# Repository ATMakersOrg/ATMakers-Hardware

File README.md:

# ATMakers-Hardware
PCB Design files and other hardware artifacts from ATMakers.org

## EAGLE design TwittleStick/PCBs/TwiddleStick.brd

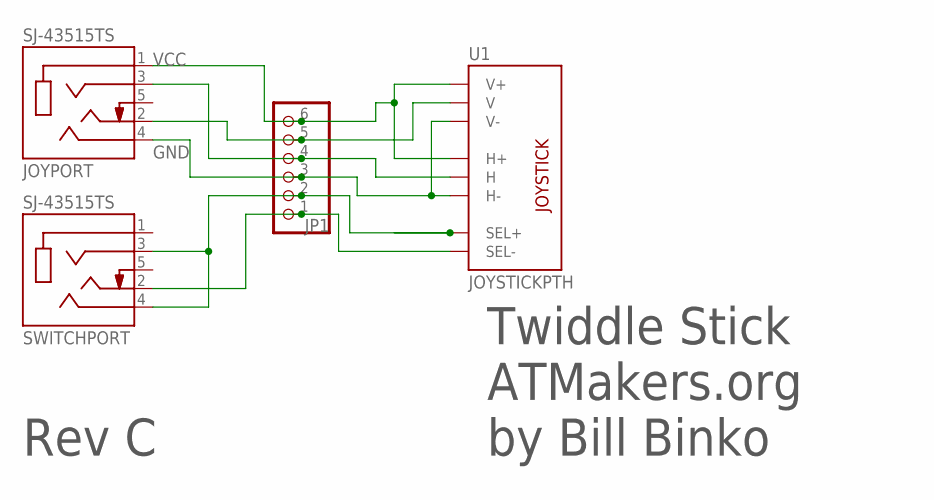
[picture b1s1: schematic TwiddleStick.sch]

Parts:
JOYPORT: SJ-43515TS; CUI_SJ-43515TS
JP1: PINHD-1X6B; 1X06-BIG
SWITCHPORT: SJ-43515TS; CUI_SJ-43515TS
U1: JOYSTICKPTH; JOYSTICK

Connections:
GND: JOYPORT.4 (RING2), JP1.3, U1.H3 (H-), U1.V3 (V-)
unnamed: JP1.2, SWITCHPORT.3 (RING1), SWITCHPORT.4 (RING2), U1.B1A (SEL+)
unnamed: JOYPORT.2 (TIP), JP1.5, U1.V2 (V)
unnamed: JOYPORT.3 (RING1), JP1.4, U1.H2 (H)
unnamed: JP1.1, SWITCHPORT.2 (TIP), U1.B2A (SEL-)
VCC: JOYPORT.1 (SLEEVE), JP1.6, U1.H1 (H+), U1.V1 (V+)

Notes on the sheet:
Twiddle Stick ATMakers.org by Bill Binko
Rev C

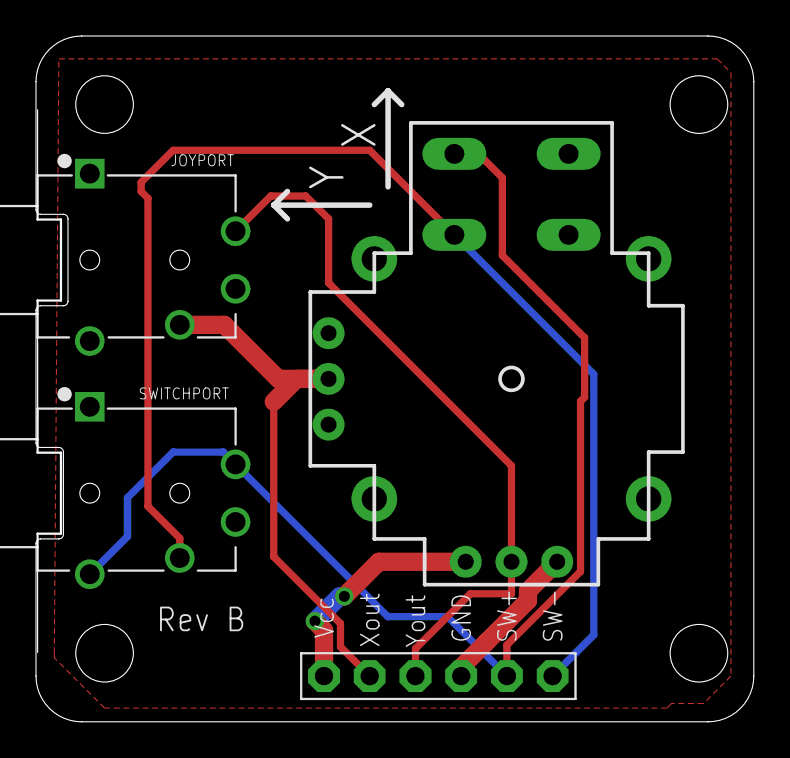
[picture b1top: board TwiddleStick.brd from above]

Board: 2 copper layers, 39.9 x 38.1 mm, 4 parts (0 on the bottom side), 6 nets.

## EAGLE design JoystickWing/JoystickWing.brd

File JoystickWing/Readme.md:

This is a PTH-only design that should be simple to assemble.  It has a FeatherWing format and should allow a microcontroller to interface with a PG-Drives powerchair controller.

The design was based off of the details in section 6 of this manual: http://sunrise.pgdrivestechnology.com/manuals/pgdt_omni_manual_SK78813-07.pdf

It is based on the Adafruit DS3502 Digital Pot breakout
https://learn.adafruit.com/ds3502-i2c-potentiometer/overview

It uses this D-Sub 9 panel-mount connector
https://www.digikey.com/products/en?keywords=5747844-4

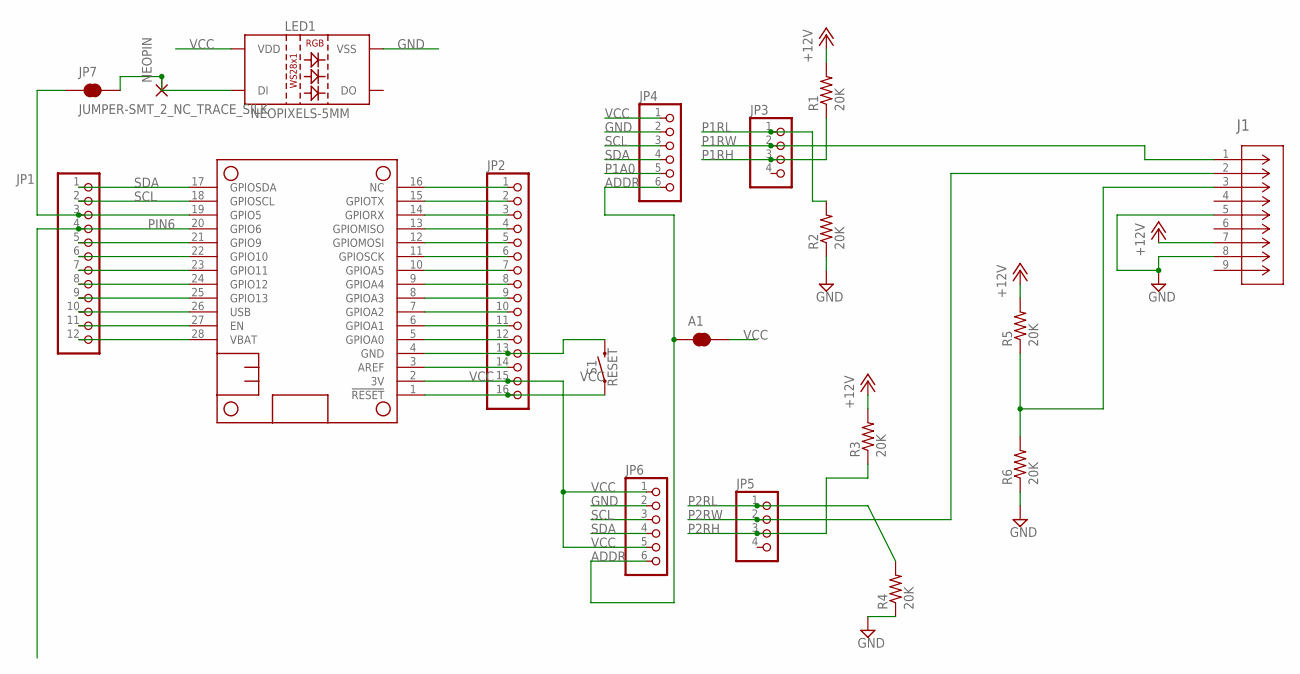
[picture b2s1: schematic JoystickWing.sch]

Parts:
A1: JUMPER-SMT_2_NC_TRACE_SILK; SMT-JUMPER_2_NC_TRACE_SILK
J1: 5747844-4; CONN_5747844-4
JP1: PINHD-1X12; 1X12
JP2: PINHD-1X16; 1X16
JP3, JP5: HEADER-1X4ROUND; 1X04_ROUND
JP4, JP6: HEADER-1X6ROUND; 1X06_ROUND
JP7: JUMPER-SMT_2_NC_TRACE_SILK; SMT-JUMPER_2_NC_TRACE_SILK
LED1: NEOPIXELS-5MM
MS1: FEATHERWING_NODIM; FEATHERWING_DIM
NEOPIN: 2,54/1,1
R1, R2, R3, R4, R5, R6: 20K; 0204/7
S1: RESET; DTS-3

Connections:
+12V: J1.7, R1.2, R3.2, R5.2
ADDR: A1.1, JP4.6, JP6.6
GND: J1.5, J1.8, JP2.13, JP4.2, JP6.2, LED1.P3 (VSS), MS1.4 (GND), R2.1, R4.1, R6.1, S1.2
unnamed: JP1.3, JP7.1, MS1.19 (GPIO5)
unnamed: JP1.5, MS1.21 (GPIO9)
unnamed: JP1.6, MS1.22 (GPIO10)
unnamed: JP1.7, MS1.23 (GPIO11)
unnamed: JP1.8, MS1.24 (GPIO12)
unnamed: J1.3, R5.1, R6.2
unnamed: JP1.9, MS1.25 (GPIO13)
unnamed: JP1.11, MS1.27 (EN)
unnamed: JP2.1, MS1.16 (NC)
unnamed: JP2.2, MS1.15 (GPIOTX)
unnamed: JP2.3, MS1.14 (GPIORX)
unnamed: JP2.4, MS1.13 (GPIOMISO)
unnamed: JP2.5, MS1.12 (GPIOMOSI)
unnamed: JP2.6, MS1.11 (GPIOSCK)
unnamed: JP2.7, MS1.10 (GPIOA5)
unnamed: JP2.8, MS1.9 (GPIOA4)
unnamed: JP2.9, MS1.8 (GPIOA3)
unnamed: JP2.10, MS1.7 (GPIOA2)
unnamed: JP2.11, MS1.6 (GPIOA1)
unnamed: JP2.12, MS1.5 (GPIOA0)
unnamed: JP2.14, MS1.3 (AREF)
unnamed: JP2.16, MS1.1 (!RESET), S1.1
unnamed: JP7.2, LED1.P1 (DI), NEOPIN.1
P1A0: JP4.5
P1RH: JP3.3, R1.1
P1RL: JP3.1, R2.2
P1RW: J1.1, JP3.2
P2RH: JP5.3, R3.1
P2RL: JP5.1, R4.2
P2RW: J1.2, JP5.2
PIN6: JP1.4, MS1.20 (GPIO6)
SCL: JP1.2, JP4.3, JP6.3, MS1.18 (GPIOSCL)
SDA: JP1.1, JP4.4, JP6.4, MS1.17 (GPIOSDA)
USB: JP1.10, MS1.26 (USB)
VBAT: JP1.12, MS1.28 (VBAT)
VCC: A1.2, JP2.15, JP4.1, JP6.1, JP6.5, LED1.P2 (VDD), MS1.2 (3V)

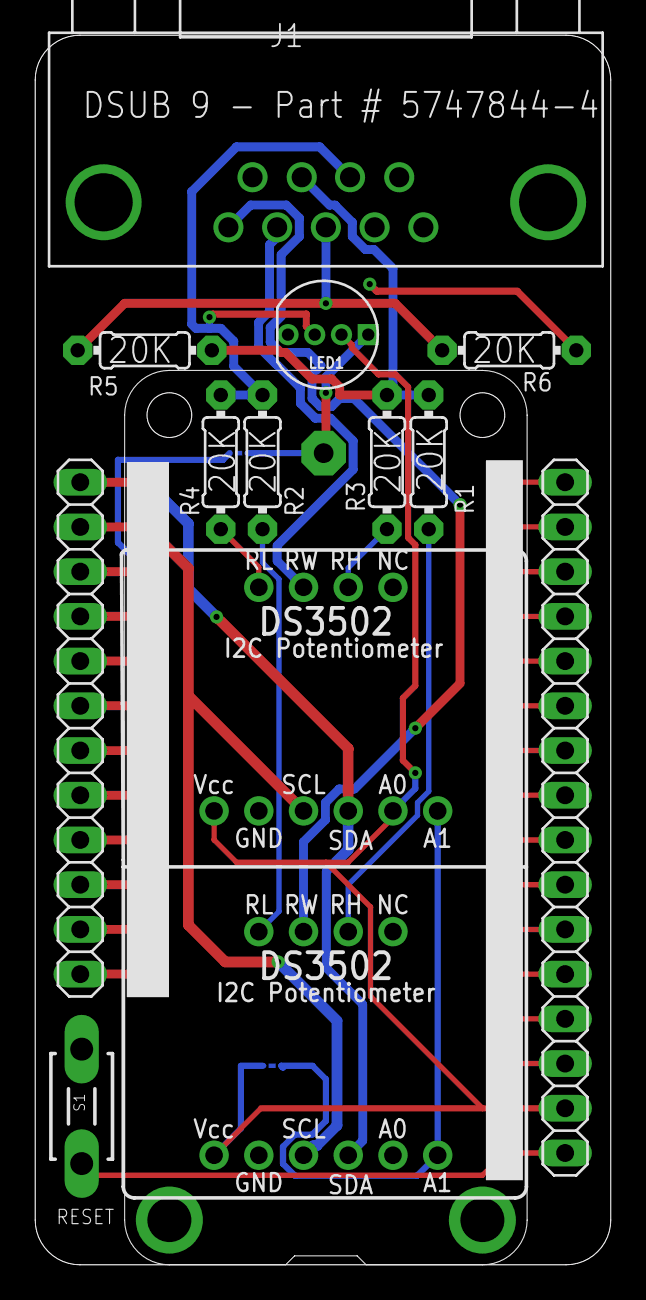
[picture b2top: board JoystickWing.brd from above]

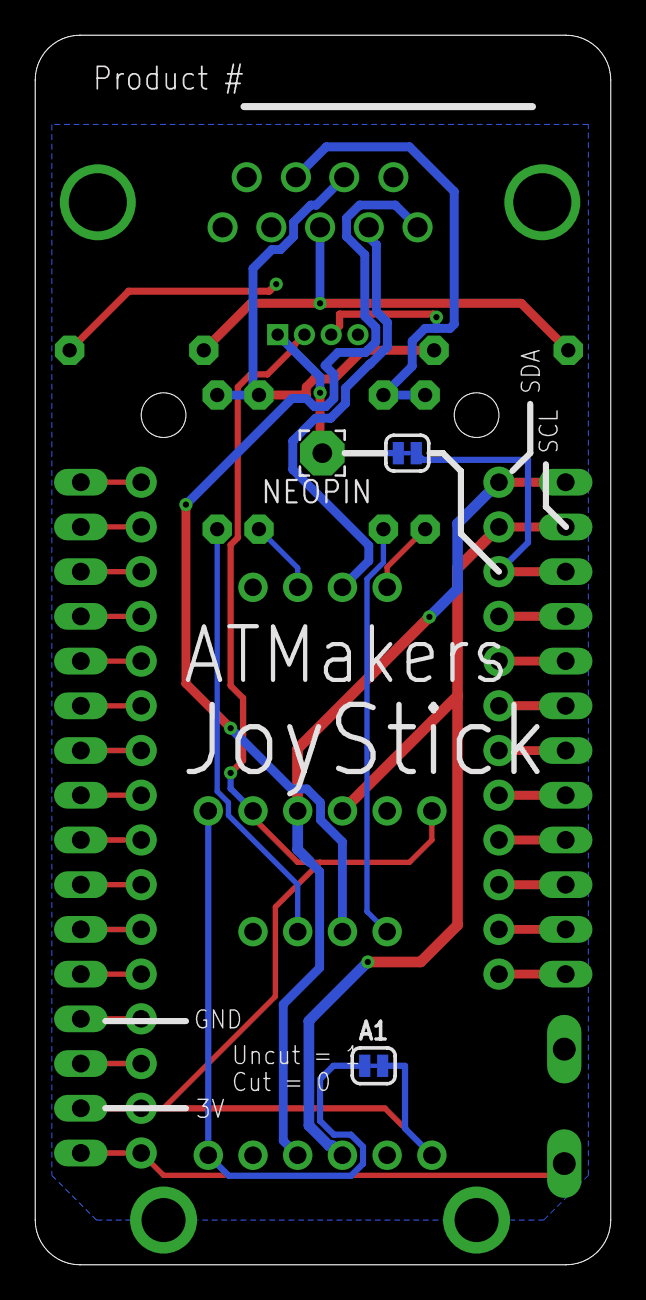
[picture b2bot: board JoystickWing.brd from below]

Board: 2 copper layers, 32.7 x 69.8 mm, 19 parts (3 on the bottom side), 38 nets.

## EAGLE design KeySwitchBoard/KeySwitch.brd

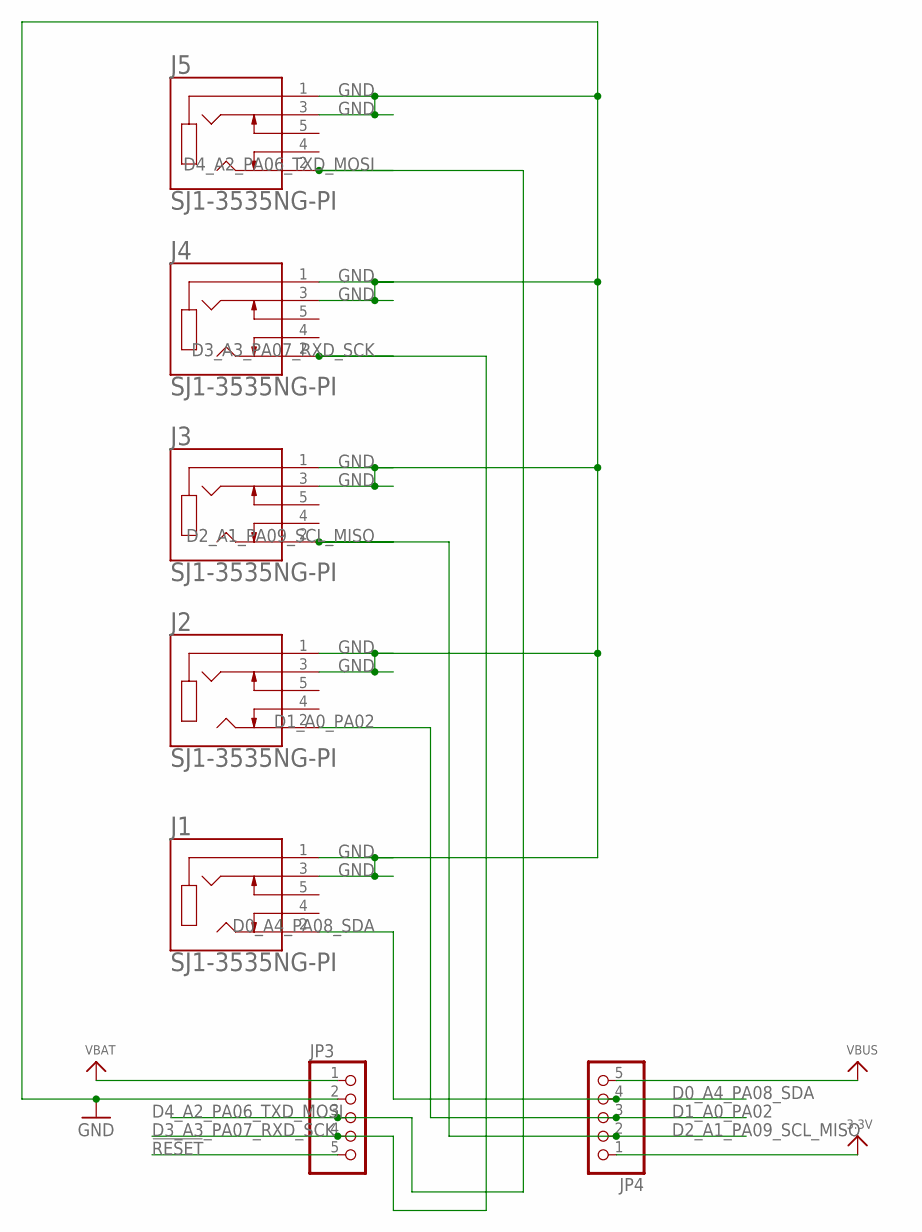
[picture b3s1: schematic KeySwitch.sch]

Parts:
J1, J2, J3, J4, J5: SJ1-3535NG-PI; CUI_SJ1-3535NG-PI
JP3, JP4: HEADER-1X576MIL; 1X05_ROUND_76

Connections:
3.3V: JP4.1
!RESET: JP3.5
D0_A4_PA08_SDA: J1.2, JP4.4
D1_A0_PA02: J2.2, JP4.3
D2_A1_PA09_SCL_MISO: J3.2, JP4.2
D3_A3_PA07_RXD_SCK: J4.2, JP3.4
D4_A2_PA06_TXD_MOSI: J5.2, JP3.3
GND: J1.1, J1.3, J2.1, J2.3, J3.1, J3.3, J4.1, J4.3, J5.1, J5.3, JP3.2
VBAT: JP3.1
VBUS: JP4.5

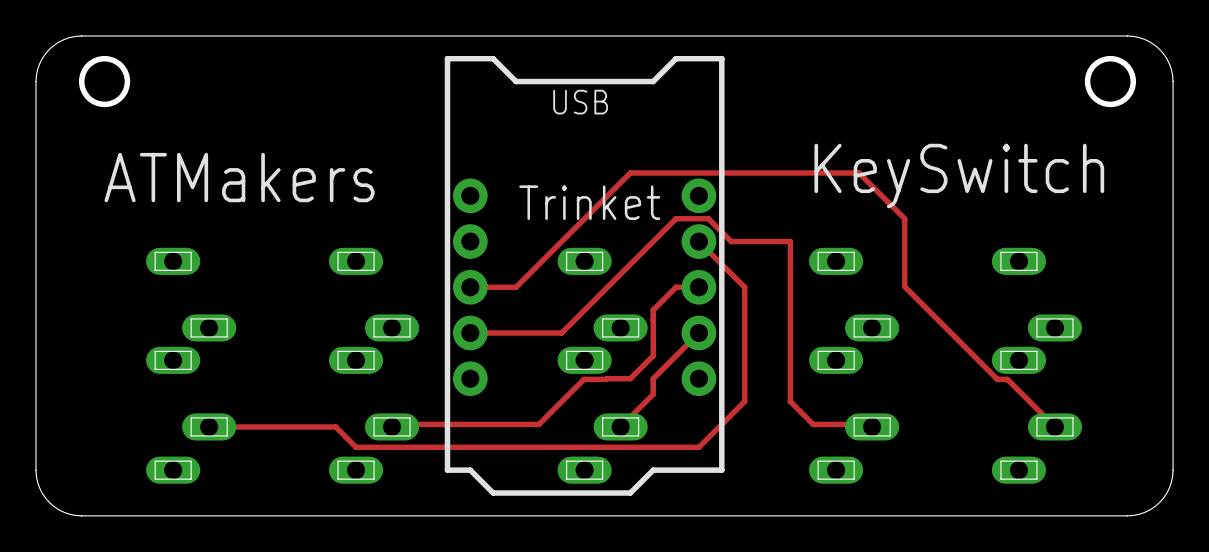
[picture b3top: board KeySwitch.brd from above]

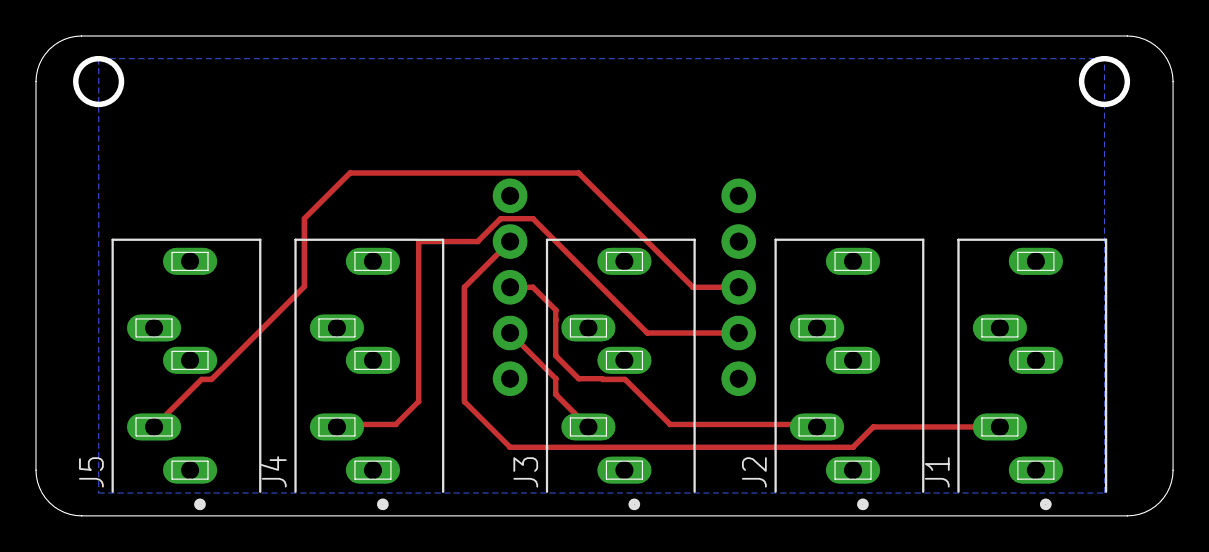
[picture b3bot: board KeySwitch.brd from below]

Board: 2 copper layers, 63.2 x 26.7 mm, 7 parts (5 on the bottom side), 6 nets.

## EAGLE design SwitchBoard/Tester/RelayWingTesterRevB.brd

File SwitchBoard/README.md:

# ATMakers-Hardware-SwitchBoard
Eagle CAD PCB Design files and other product information for the 5-Relay Switchboard Feather Wing.

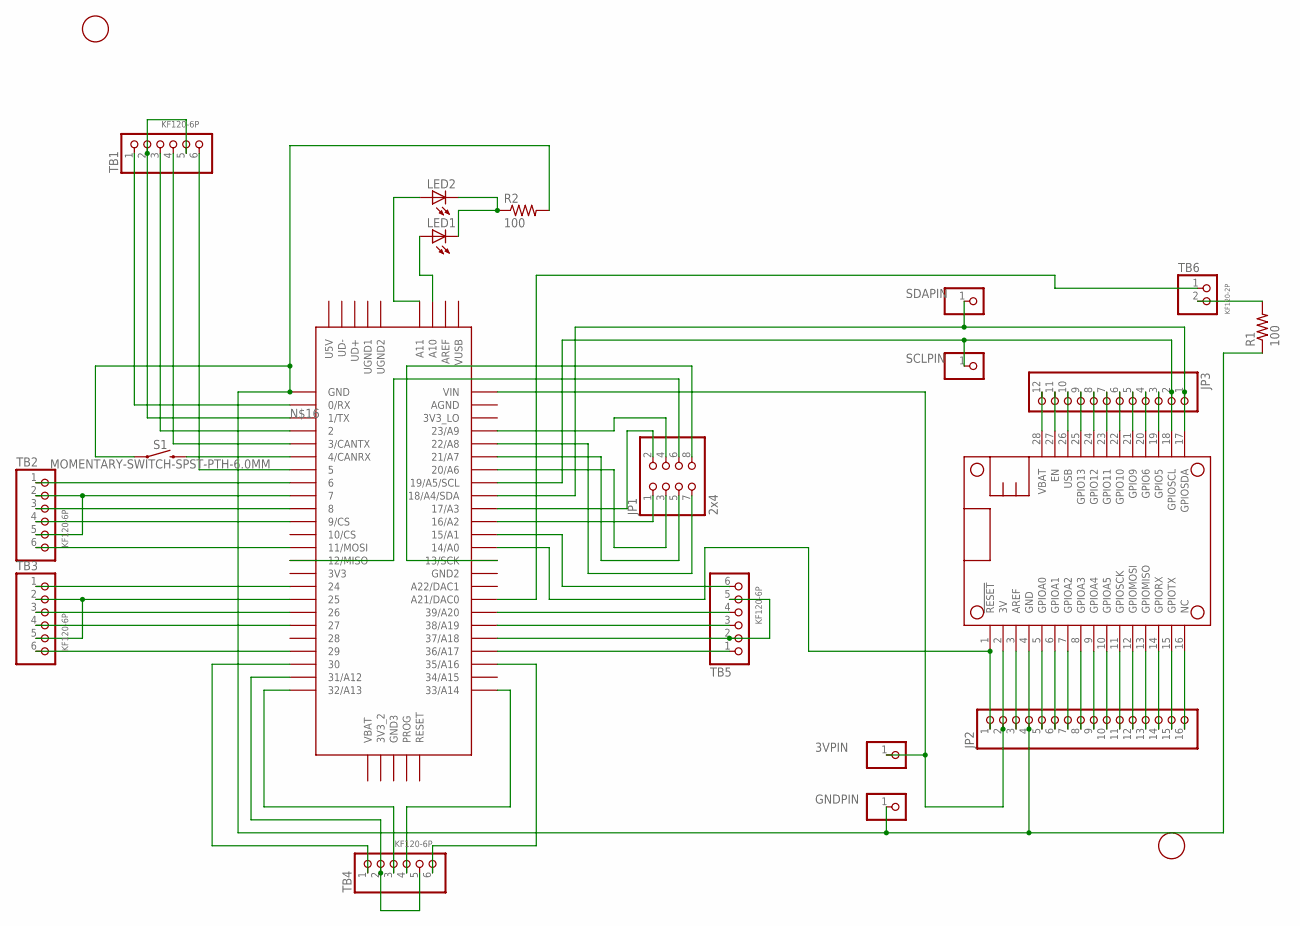
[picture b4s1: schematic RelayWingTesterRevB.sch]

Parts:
3VPIN: PINHD-1X1; 1X01
GNDPIN: PINHD-1X1; 1X01
JP1: 2x4; 2X04
JP2: PINHD-1X16; 1X16
JP3: PINHD-1X12; 1X12
LED1, LED2: LED5MM
MS1: FEATHERWING_NODIM; FEATHERWING_DIM
R1, R2: 100; 0207/10
S1: MOMENTARY-SWITCH-SPST-PTH-6.0MM; TACTILE_SWITCH_PTH_6.0MM
SCLPIN: PINHD-1X1; 1X01
SDAPIN: PINHD-1X1; 1X01
TB1, TB2, TB3, TB4, TB5: KF120-6P; KF120-6P_ROUND
TB6: KF120-2P; KF120-2P_ROUND
U$2, U$3: FIDUCIAL; FIDUCIAL_1MM
U$4: TEENSY_3.5/3.6

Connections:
3V: 3VPIN.1, JP2.2, MS1.2 (3V), U$4.VIN
GND: GNDPIN.1, JP2.4, MS1.4 (GND), R1.1, R2.2, S1.1, U$4.GND
unnamed: JP2.3, MS1.3 (AREF)
unnamed: JP3.1, MS1.17 (GPIOSDA), SDAPIN.1, U$4.18/A4/SDA
unnamed: JP2.5, MS1.5 (GPIOA0)
unnamed: JP2.6, MS1.6 (GPIOA1)
unnamed: JP2.7, MS1.7 (GPIOA2)
unnamed: JP2.8, MS1.8 (GPIOA3)
unnamed: JP2.9, MS1.9 (GPIOA4)
unnamed: JP2.10, MS1.10 (GPIOA5)
unnamed: JP2.11, MS1.11 (GPIOSCK)
unnamed: JP2.12, MS1.12 (GPIOMOSI)
unnamed: JP2.13, MS1.13 (GPIOMISO)
unnamed: JP2.14, MS1.14 (GPIORX)
unnamed: JP2.15, MS1.15 (GPIOTX)
unnamed: JP2.16, MS1.16 (NC)
unnamed: JP3.3, MS1.19 (GPIO5)
unnamed: TB1.1, U$4.0/RX
unnamed: TB1.2, TB1.5, U$4.1/TX
unnamed: R1.2, TB6.2
unnamed: JP3.4, MS1.20 (GPIO6)
unnamed: JP3.5, MS1.21 (GPIO9)
unnamed: JP3.6, MS1.22 (GPIO10)
unnamed: JP3.7, MS1.23 (GPIO11)
unnamed: JP3.8, MS1.24 (GPIO12)
unnamed: TB1.3, U$4.2
unnamed: TB1.4, U$4.3/CANTX
unnamed: S1.3 (2), U$4.4/CANRX
unnamed: TB1.6, U$4.5
unnamed: TB2.1, U$4.6
unnamed: TB2.2, TB2.5, U$4.7
unnamed: TB2.3, U$4.8
unnamed: TB2.4, U$4.9/CS
unnamed: TB2.6, U$4.11/MOSI
unnamed: TB3.1, U$4.24
unnamed: TB3.2, TB3.5, U$4.25
unnamed: TB3.3, U$4.26
unnamed: TB3.4, U$4.27
unnamed: TB3.6, U$4.29
unnamed: TB4.1, U$4.30
unnamed: TB4.2, TB4.5, U$4.31/A12
unnamed: TB4.3, U$4.32/A13
unnamed: TB4.4, U$4.33/A14
unnamed: TB4.6, U$4.35/A16
unnamed: TB5.1, U$4.36/A17
unnamed: TB5.2, TB5.5, U$4.37/A18
unnamed: TB5.3, U$4.38/A19
unnamed: TB5.4, U$4.39/A20
unnamed: JP3.9, MS1.25 (GPIO13)
unnamed: TB5.6, U$4.15/A1
unnamed: TB6.1, U$4.21/DAC0 (A21/DAC0)
unnamed: JP1.1, U$4.16/A2
unnamed: JP1.2, U$4.17/A3
unnamed: JP1.3, U$4.20/A6
unnamed: JP1.5, U$4.21/A7
unnamed: JP1.7, U$4.22/A8
unnamed: JP1.4, U$4.23/A9
unnamed: JP3.11, MS1.27 (EN)
unnamed: JP1.6, U$4.12/MISO
unnamed: JP1.8, U$4.13/SCK
unnamed: LED2.A, U$4.A11
unnamed: LED1.A, U$4.A10
unnamed: LED1.K (C), LED2.K (C), R2.1
RESET: JP2.1, MS1.1 (!RESET), U$4.14/A0
SCL: JP3.2, MS1.18 (GPIOSCL), SCLPIN.1, U$4.19/A5/SCL
USB: JP3.10, MS1.26 (USB)
VBAT: JP3.12, MS1.28 (VBAT)

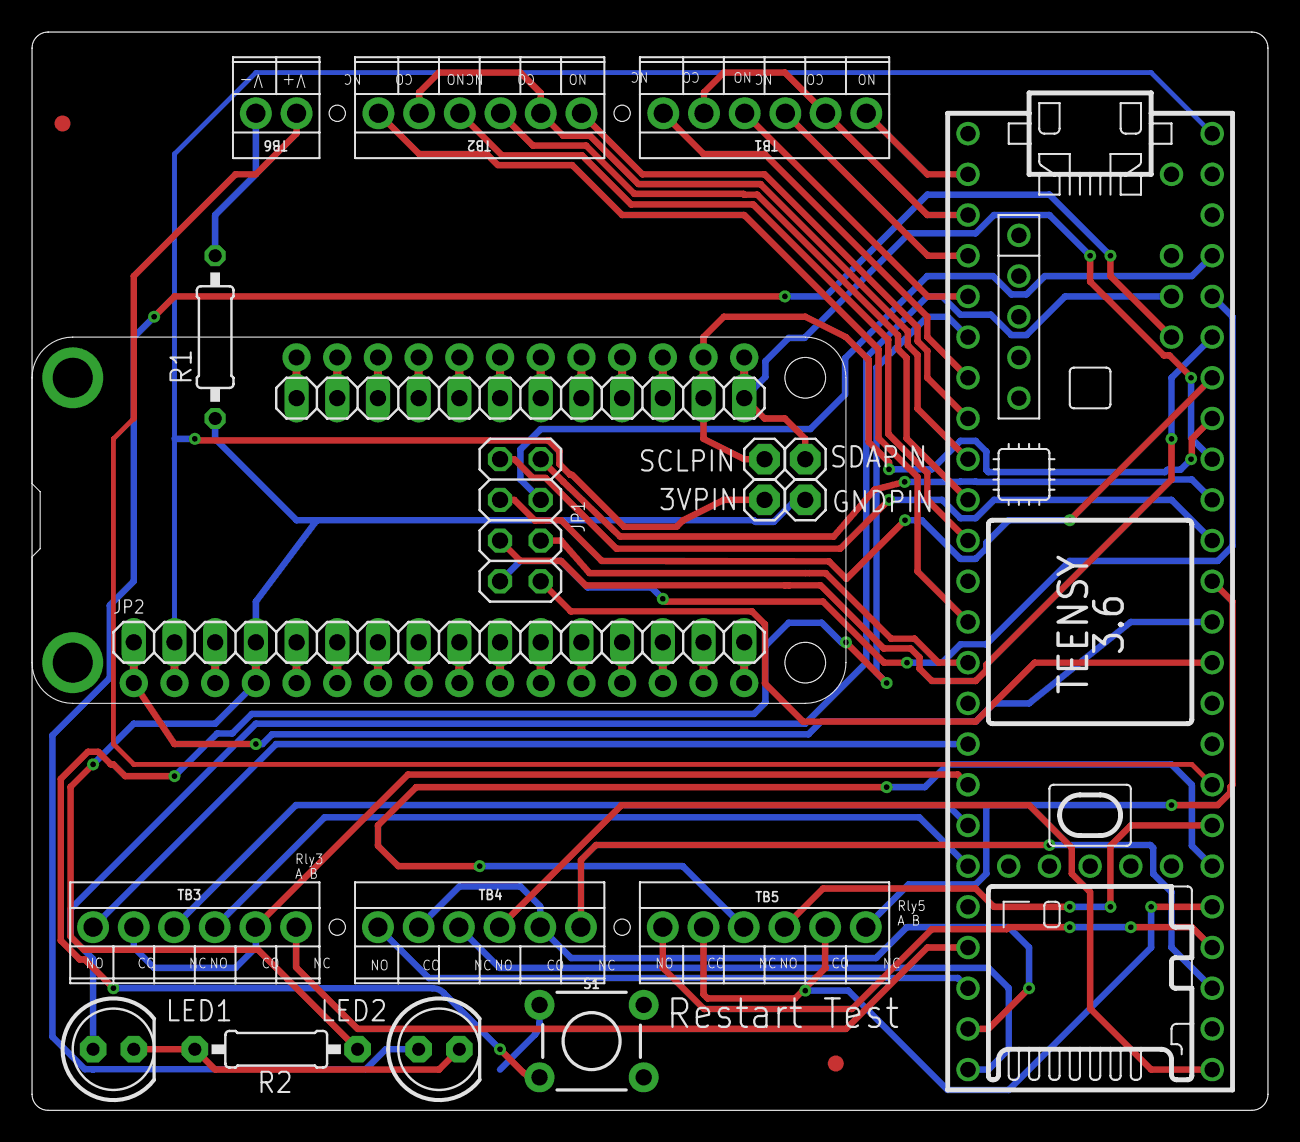
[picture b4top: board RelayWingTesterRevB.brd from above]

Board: 2 copper layers, 77.1 x 67.3 mm, 22 parts (0 on the bottom side), 67 nets.

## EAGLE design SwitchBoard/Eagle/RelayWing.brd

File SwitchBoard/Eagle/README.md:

# ATMakers-Hardware-SwitchBoard-Eagle
Eagle CAD PCB Design files.

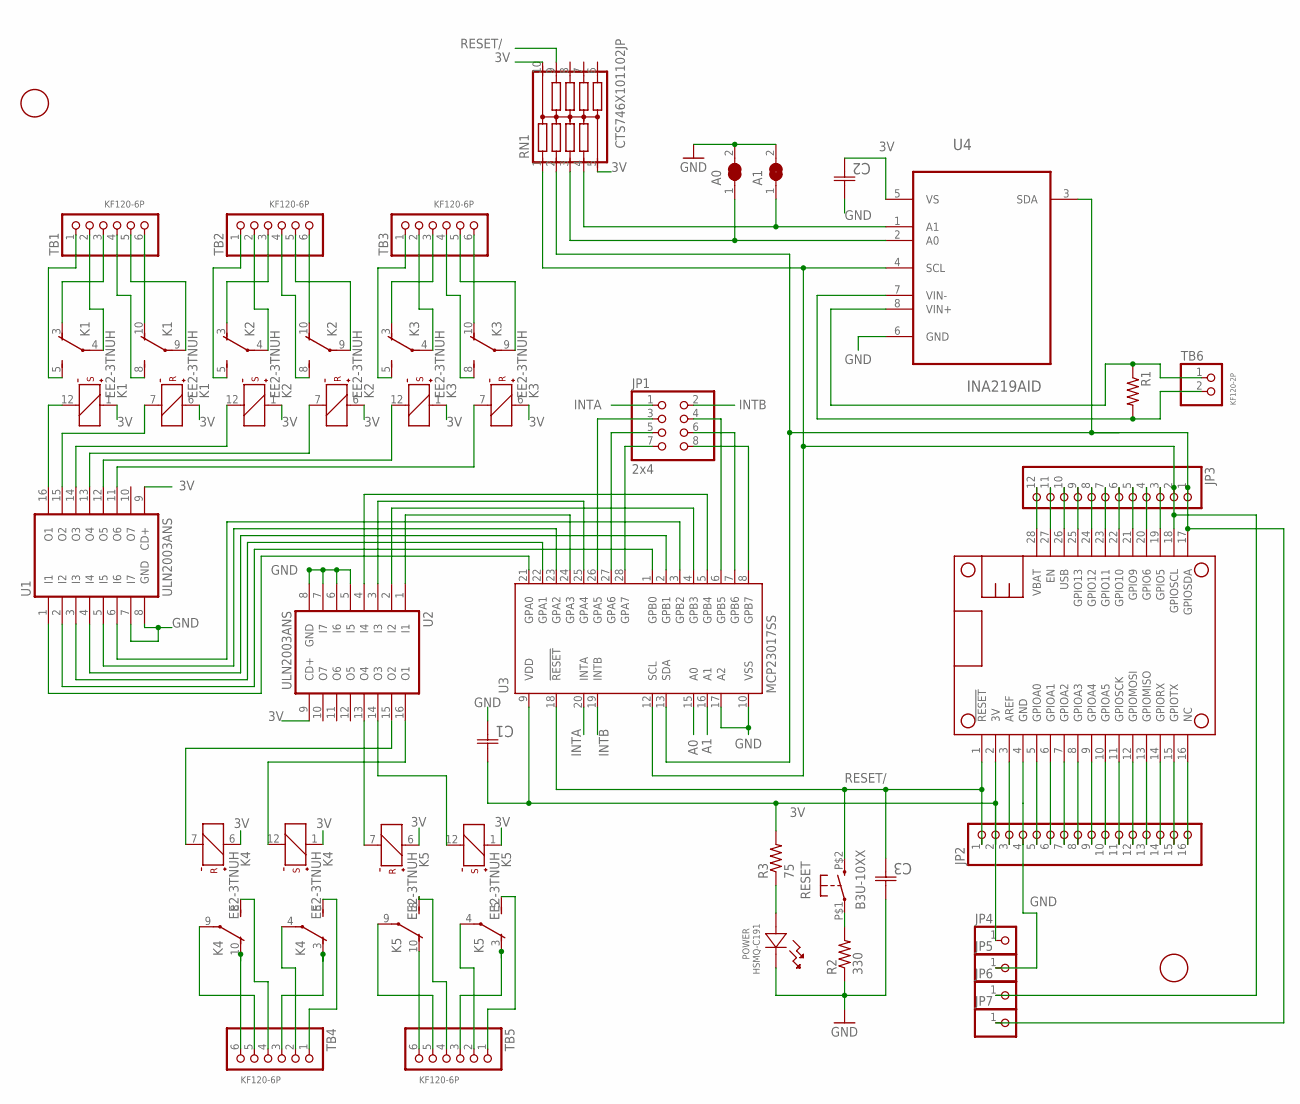
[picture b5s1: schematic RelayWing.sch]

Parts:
A0, A1: SJW-SHORTED
C1, C2, C3: MUR-1220-CAP; CAPC2012
JP1: 2x4; 2X04
JP2: PINHD-1X16; 1X16
JP3: PINHD-1X12; 1X12
JP4, JP5, JP6, JP7: PINHD-1X1CB; 1X01-CLEANBIG
K1, K2, K3, K4, K5: EE2-3TNUH; NUH
MS1: FEATHERWING_NODIM; FEATHERWING_DIM
POWER: HSMQ-C191; LED3_HSMX-C120
R1: 0.1; M3216
R2: 330; R0603
R3: 75; R0603
RESET: B3U-10XX
RN1: CTS746X101102JP; CTS746X101
TB1, TB2, TB3, TB4, TB5: KF120-6P; KF120-6P_ROUND
TB6: KF120-2P; KF120-2P_ROUND
U1, U2: ULN2003ANS; SO16-NS
U3: MCP23017SS; SSOP28
U4: INA219AID; SOIC127P600X175-8N
U$2, U$3: FIDUCIAL; FIDUCIAL_1MM

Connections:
3V: C1.1 (C1), C2.2 (C2), JP2.2, JP4.1, K1.1 (+), K1.6 (+), K2.1 (+), K2.6 (+), K3.1 (+), K3.6 (+), K4.1 (+), K4.6 (+), K5.1 (+), K5.6 (+), MS1.2 (3V), R3.2, RN1.5 (5C), RN1.10 (10C), U1.9 (CD+), U2.9 (CD+), U3.9 (VDD), U4.5 (VS)
A0: A0.1, RN1.3, U3.15 (A0), U4.2 (A0)
A1: A1.1, RN1.4, U3.16 (A1), U4.1 (A1)
GND: A0.2, A1.2, C1.2 (C2), C2.1 (C1), C3.1 (C1), JP2.4, JP5.1, MS1.4 (GND), POWER.1 (11), R2.1, U1.7 (I7), U1.8 (GND), U2.5 (I5), U2.6 (I6), U2.7 (I7), U2.8 (GND), U3.10 (VSS), U3.17 (A2), U4.6 (GND)
GPA0: U1.1 (I1), U3.21 (GPA0)
GPA1: U1.3 (I3), U3.22 (GPA1)
GPA2: U1.5 (I5), U3.23 (GPA2)
GPA3: U2.1 (I1), U3.24 (GPA3)
GPA4: U2.3 (I3), U3.25 (GPA4)
GPA5: JP1.3, U3.26 (GPA5)
GPA6: JP1.5, U3.27 (GPA6)
GPA7: JP1.7, U3.28 (GPA7)
GPB0: U1.2 (I2), U3.1 (GPB0)
GPB1: U1.4 (I4), U3.2 (GPB1)
GPB2: U1.6 (I6), U3.3 (GPB2)
GPB3: U2.2 (I2), U3.4 (GPB3)
GPB4: U2.4 (I4), U3.5 (GPB4)
GPB5: JP1.4, U3.6 (GPB5)
GPB6: JP1.6, U3.7 (GPB6)
GPB7: JP1.8, U3.8 (GPB7)
INTA: JP1.1, U3.20 (INTA)
INTB: JP1.2, U3.19 (INTB)
K1-RESET: K1.7 (-), U1.15 (O2)
K1-SET: K1.12 (-), U1.16 (O1)
K1A-CO: K1.4, TB1.2
K1A-NC: K1.3 (O), TB1.3
K1A-NO: K1.5 (S), TB1.1
K1B-CO: K1.9, TB1.5
K1B-NC: K1.10 (O), TB1.6
K1B-NO: K1.8 (S), TB1.4
K2-RESET: K2.7 (-), U1.13 (O4)
K2-SET: K2.12 (-), U1.14 (O3)
K2A-CO: K2.4, TB2.2
K2A-NC: K2.3 (O), TB2.3
K2A-NO: K2.5 (S), TB2.1
K2B-CO: K2.9, TB2.5
K2B-NC: K2.10 (O), TB2.6
K2B-NO: K2.8 (S), TB2.4
K3-RESET: K3.7 (-), U1.11 (O6)
K3-SET: K3.12 (-), U1.12 (O5)
K3A-CO: K3.4, TB3.2
K3A-NC: K3.3 (O), TB3.3
K3A-NO: K3.5 (S), TB3.1
K3B-CO: K3.9, TB3.5
K3B-NC: K3.10 (O), TB3.6
K3B-NO: K3.8 (S), TB3.4
K4-RESET: K4.7 (-), U2.15 (O2)
K4-SET: K4.12 (-), U2.16 (O1)
K4A-CO: K4.4, TB4.2
K4A-N0: K4.5 (S), TB4.1
K4A-NC: K4.3 (O), TB4.3
K4B-CO: K4.9, TB4.5
K4B-NC: K4.10 (O), TB4.6
K4B-NO: K4.8 (S), TB4.4
K5-RESET: K5.7 (-), U2.13 (O4)
K5-SET: K5.12 (-), U2.14 (O3)
K5A-CO: K5.4, TB5.2
K5A-NC: K5.3 (O), TB5.3
K5A-NO: K5.5 (S), TB5.1
K5B-CO: K5.9, TB5.5
K5B-NC: K5.10 (O), TB5.6
K5B-NO: K5.8 (S), TB5.4
unnamed: JP2.3, MS1.3 (AREF)
unnamed: POWER.2 (33), R3.1
unnamed: JP2.5, MS1.5 (GPIOA0)
unnamed: JP2.6, MS1.6 (GPIOA1)
unnamed: JP2.7, MS1.7 (GPIOA2)
unnamed: JP2.8, MS1.8 (GPIOA3)
unnamed: JP2.9, MS1.9 (GPIOA4)
unnamed: JP2.10, MS1.10 (GPIOA5)
unnamed: JP2.11, MS1.11 (GPIOSCK)
unnamed: JP2.12, MS1.12 (GPIOMOSI)
unnamed: JP2.13, MS1.13 (GPIOMISO)
unnamed: JP2.14, MS1.14 (GPIORX)
unnamed: JP2.15, MS1.15 (GPIOTX)
unnamed: JP2.16, MS1.16 (NC)
unnamed: JP3.3, MS1.19 (GPIO5)
unnamed: JP3.4, MS1.20 (GPIO6)
unnamed: JP3.5, MS1.21 (GPIO9)
unnamed: JP3.6, MS1.22 (GPIO10)
unnamed: JP3.7, MS1.23 (GPIO11)
unnamed: JP3.8, MS1.24 (GPIO12)
unnamed: R2.2, RESET.P$1
unnamed: JP3.9, MS1.25 (GPIO13)
unnamed: JP3.11, MS1.27 (EN)
RESET/: C3.2 (C2), JP2.1, MS1.1 (!RESET), RESET.P$2 (S), RN1.9, U3.18 (!RESET)
SCL: JP3.2, JP6.1, MS1.18 (GPIOSCL), RN1.1, U3.12 (SCL), U4.4 (SCL)
SDA: JP3.1, JP7.1, MS1.17 (GPIOSDA), RN1.2, U3.13 (SDA), U4.3 (SDA)
USB: JP3.10, MS1.26 (USB)
VBAT: JP3.12, MS1.28 (VBAT)
VIN+: R1.1, TB6.1, U4.8 (VIN+)
VIN-: R1.2, TB6.2, U4.7 (VIN-)

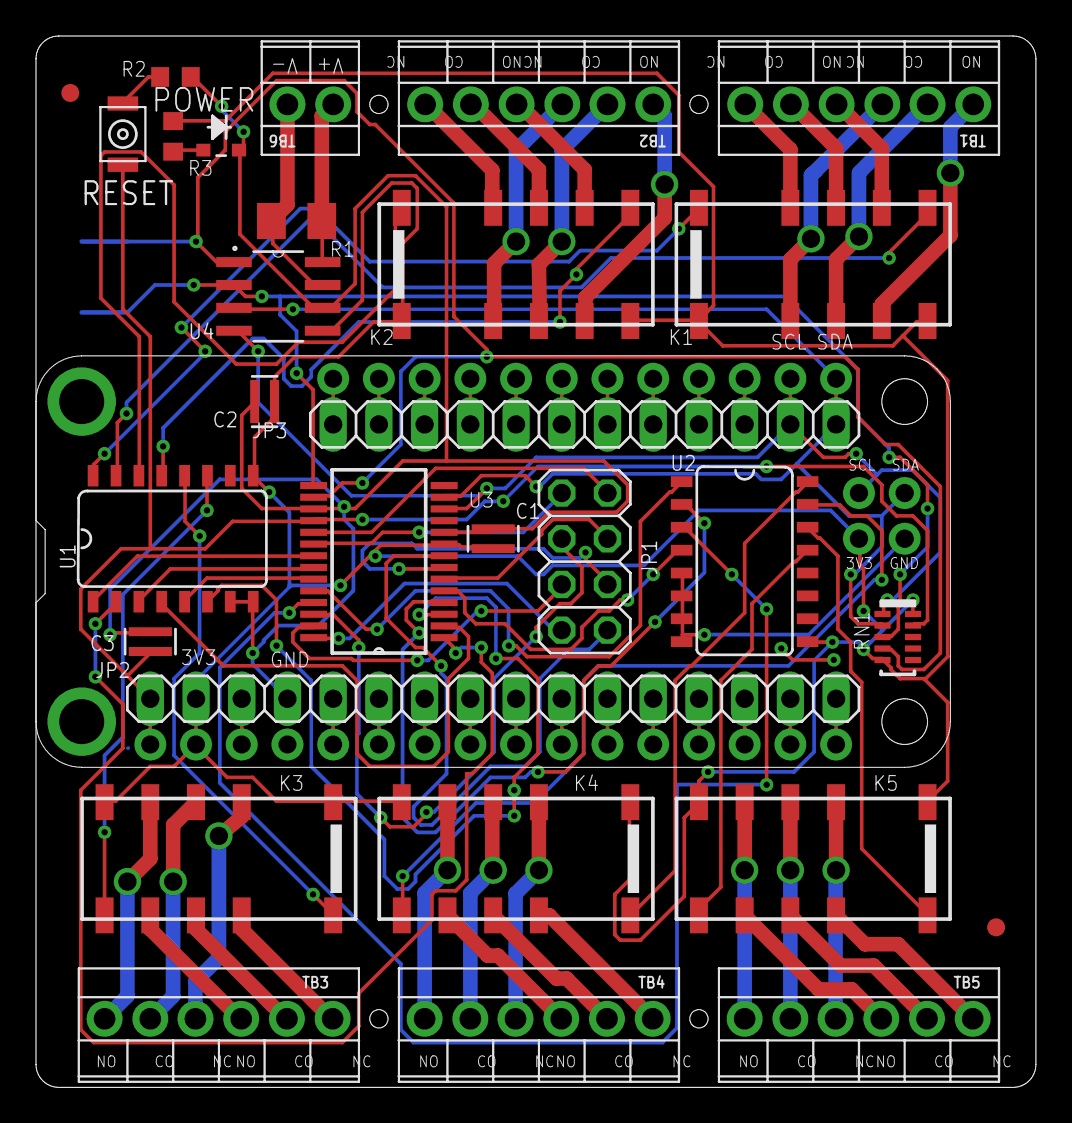
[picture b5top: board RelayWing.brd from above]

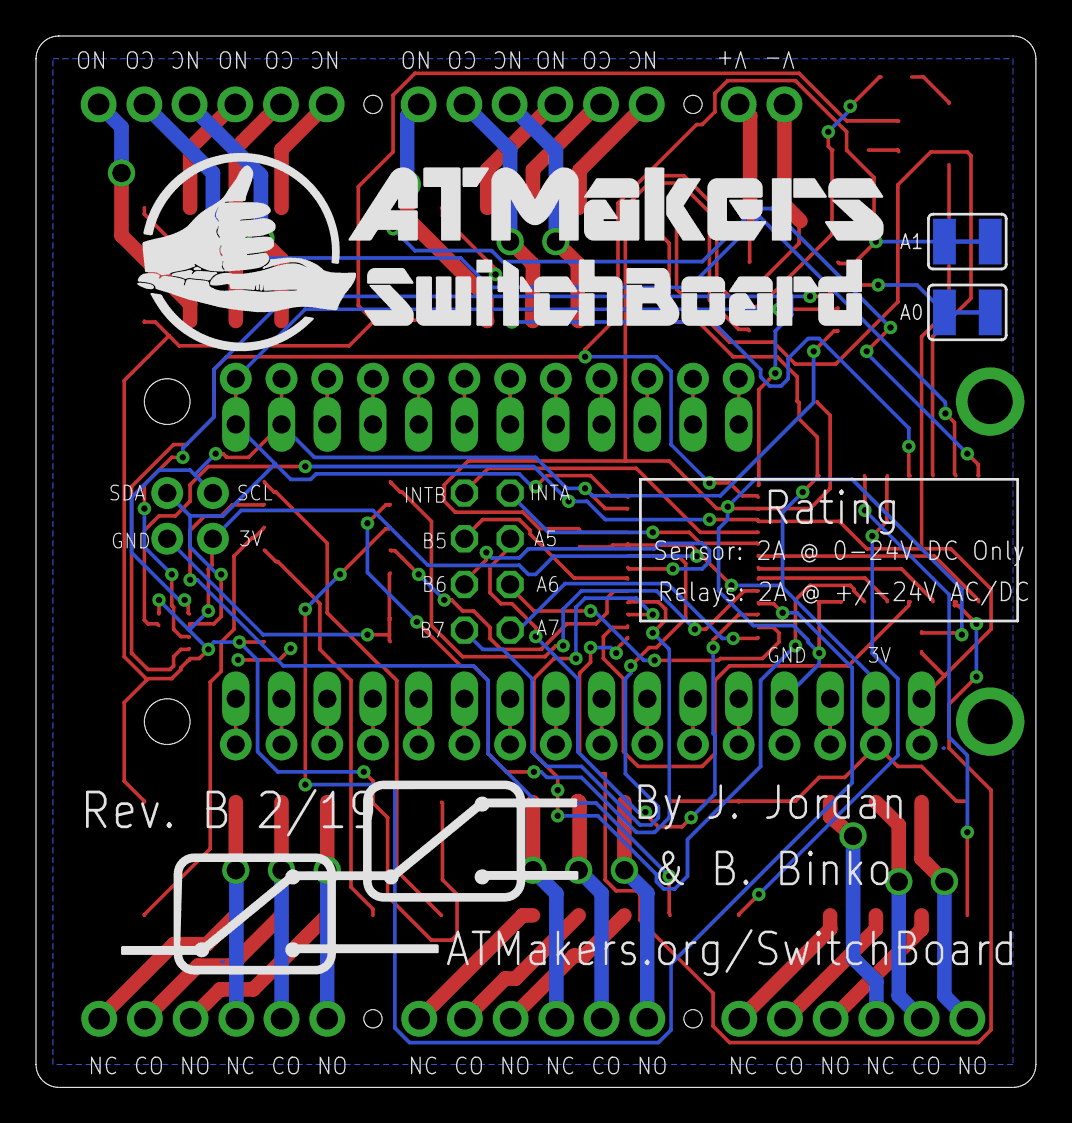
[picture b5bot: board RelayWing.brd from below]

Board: 2 copper layers, 55.5 x 58.4 mm, 36 parts (2 on the bottom side), 92 nets.

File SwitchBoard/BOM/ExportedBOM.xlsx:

Part | Value | Device | Package | Description | MF | MPN | OC_FARNELL | OC_NEWARK | PACKAGE | PN | SUPPLIER
A0 |  | SJW-SHORTED | SJW-SHORTED | SMD solder JUMPER
A1 |  | SJW-SHORTED | SJW-SHORTED | SMD solder JUMPER
C1 | MUR-1220-CAP | MUR-1220-CAP | CAPC2012 | CAPACITOR, 0805
C2 | MUR-1220-CAP | MUR-1220-CAP | CAPC2012 | CAPACITOR, 0805
JP1 | 2x4 | PINHD-2X4 | 2X04 | PIN HEADER
JP2 |  | PINHD-1X16 | 1X16 | PIN HEADER
JP3 |  | PINHD-1X12 | 1X12 | PIN HEADER
K1 | EE2-3TNUH | EE2-3TNUH | NUH | TX Relay 2 coil latching |  |  |  |  |  | EE2-3TNUH
K2 | EE2-3TNUH | EE2-3TNUH | NUH | TX Relay 2 coil latching |  |  |  |  |  | EE2-3TNUH
K3 | EE2-3TNUH | EE2-3TNUH | NUH | TX Relay 2 coil latching |  |  |  |  |  | EE2-3TNUH
K4 | EE2-3TNUH | EE2-3TNUH | NUH | TX Relay 2 coil latching |  |  |  |  |  | EE2-3TNUH
K5 | EE2-3TNUH | EE2-3TNUH | NUH | TX Relay 2 coil latching |  |  |  |  |  | EE2-3TNUH
MS1 | FEATHERWING_NODIM | FEATHERWING_NODIM | FEATHERWING_DIM
PWR |  | LEDSMT1206 | 1206 | LED
R1 | 0.1 | R-US_M3216 | M3216 | RESISTOR, American symbol
RESET | B3U-10XX | B3U-10XX | B3U-10XX | OMRON SWITCH
RN1 | CTS746X101 | CTS746X101 | CTS746X101 | Network Resistor CTS 746 Series Leadless Surface Mount
TB1 | KF120-6P | KF120-6P | KF120-6P_ROUND | Kaweei KF120-6P
TB2 | KF120-6P | KF120-6P | KF120-6P_ROUND | Kaweei KF120-6P
TB3 | KF120-6P | KF120-6P | KF120-6P_ROUND | Kaweei KF120-6P
TB4 | KF120-6P | KF120-6P | KF120-6P_ROUND | Kaweei KF120-6P
TB5 | KF120-6P | KF120-6P | KF120-6P_ROUND | Kaweei KF120-6P
TB6 | KF120-2P | KF120-2P | KF120-2P_ROUND | Kaweei KF120-2P
U$2 | FIDUCIAL | FIDUCIAL | FIDUCIAL_1MM | For use by pick and place machines to calibrate the vision/machine, 1mm
U$3 | FIDUCIAL | FIDUCIAL | FIDUCIAL_1MM | For use by pick and place machines to calibrate the vision/machine, 1mm
U1 | ULN2003ANS | ULN2003ANS | SO16-NS | DRIVER ARRAY
U2 | ULN2003ANS | ULN2003ANS | SO16-NS | DRIVER ARRAY
U3 | MCP23017SS | MCP23017SS | SSOP28 | http://ww1.microchip.com/downloads/en/DeviceDoc/21952a.pdf | MICROCHIP | MCP23017-E/SS | 1467674 | 31K2960
U4 | INA219AID | INA219AID | SOIC127P600X175-8N | CURRENT/ POWER MONITOR |  | INA219AID | - | 45P7635 | SOIC-8 |  | Texas Instruments

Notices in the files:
parts and their libraries:
microbuilder: This work is placed in the public domain, and may be freely used for commercial and non-commercial work with the following conditions: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
SparkFun-Jumpers: Licensing: Creative Commons ShareAlike 4.0 International - https://creativecommons.org/licenses/by-sa/4.0
